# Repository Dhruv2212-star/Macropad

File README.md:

this summer vacation i got to know about hackclub's programs and i decided to take up a challenge to stop bed rotting and learn something new and i found the perfect starting project,
i learnt many skills here such as PCB making, CAD skills and slight firmware making skills. it gave me new set of skills that i'll be using for future projects!

the project i made uses 3x3 key layout in which we can set each key to have a custom function

the project is split into 2 parts:
1. PCB designing
2. CAD designing

PCB designing- is done on kicad where you first make a schematic of the components and you then route the traces to finalise the PCB 
CAD- the case is made using CAD software, it is designed for the pcb to be exposed to keep a hobbyst vibe and also minimal plastic ussage

both of these come together with m3 screws and heat inserts embeded into the PLA case 

Made the sketch in kicad 

finalised the PCB traces and design 

the assembly file 

Made the case in a single piece and with mounts for m3 screws so that it stays in place 

Made the Top case

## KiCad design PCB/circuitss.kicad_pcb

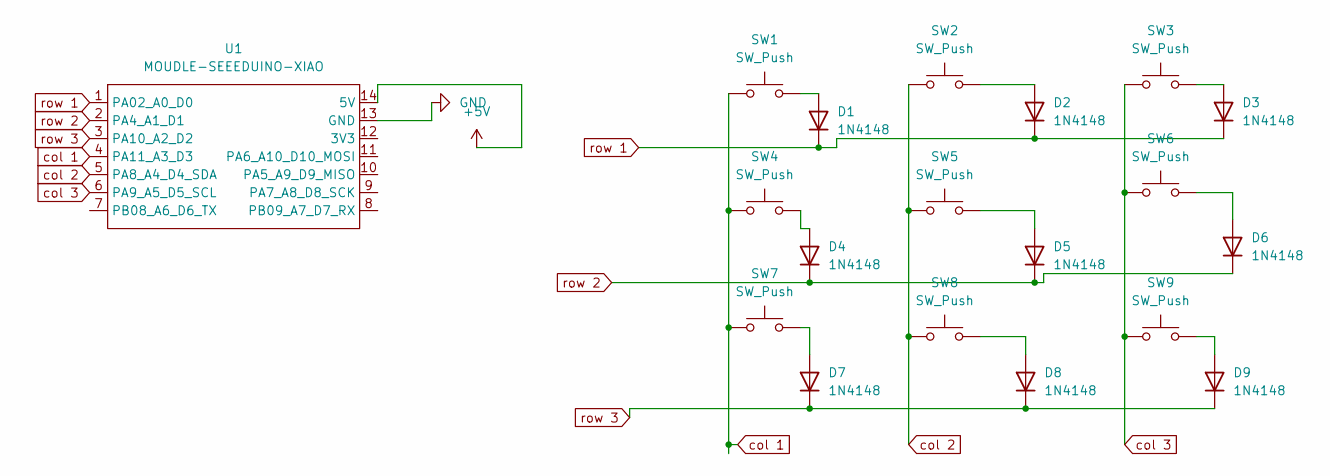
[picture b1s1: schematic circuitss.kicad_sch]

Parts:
D1, D2, D3, D4, D5, D6, D7, D8, D9: 1N4148; D_DO-35_SOD27_P7.62mm_Horizontal
SW1, SW2, SW3, SW4, SW5, SW6, SW7, SW8, SW9: SW_Push; SW_Cherry_MX_1.00u_PCB
U1: MOUDLE-SEEEDUINO-XIAO; XIAO-Generic-Hybrid-14P-2.54-21X17.8MM

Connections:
+5V: U1.14 (5V)
GND: U1.13 (GND)
unnamed: D1.2 (A), SW1.2
unnamed: D2.2 (A), SW2.2
unnamed: D3.2 (A), SW3.2
unnamed: D4.2 (A), SW4.2
unnamed: D5.2 (A), SW5.2
unnamed: D6.2 (A), SW6.2
unnamed: D7.2 (A), SW7.2
unnamed: D8.2 (A), SW8.2
unnamed: D9.2 (A), SW9.2
col 1: SW1.1, SW4.1, SW7.1, U1.4 (PA11_A3_D3)
col 2: SW2.1, SW5.1, SW8.1, U1.5 (PA8_A4_D4_SDA)
col 3: SW3.1, SW6.1, SW9.1, U1.6 (PA9_A5_D5_SCL)
row 1: D1.1 (K), D2.1 (K), D3.1 (K), U1.1 (PA02_A0_D0)
row 2: D4.1 (K), D5.1 (K), D6.1 (K), U1.2 (PA4_A1_D1)
row 3: D7.1 (K), D8.1 (K), D9.1 (K), U1.3 (PA10_A2_D2)

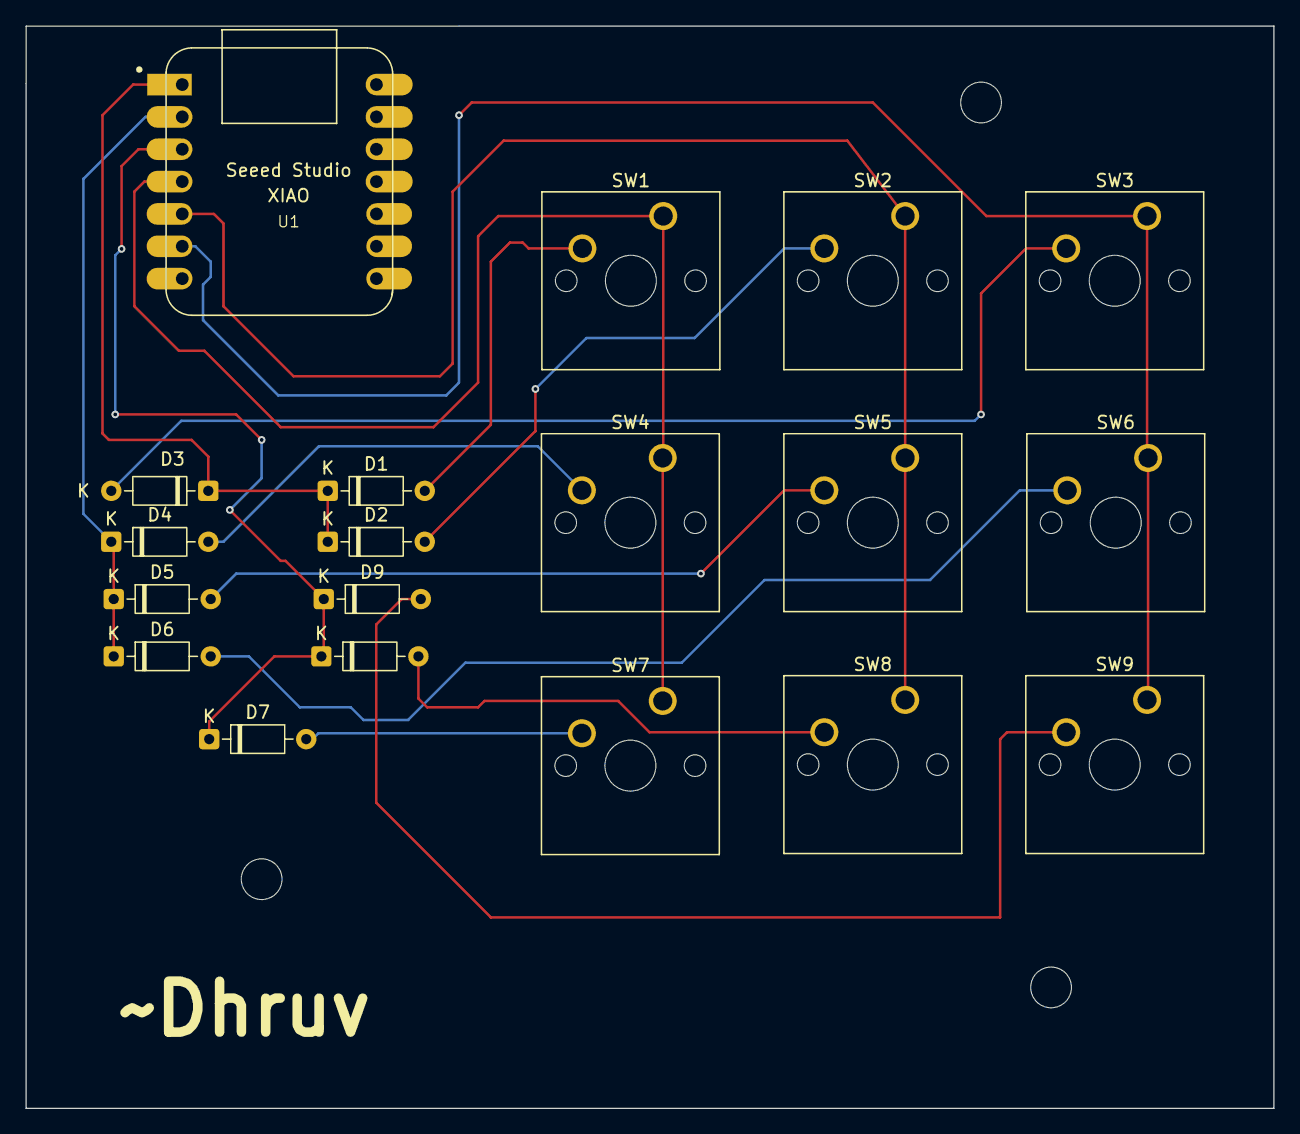
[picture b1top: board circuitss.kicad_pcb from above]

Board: 2 copper layers, 98.0 x 85.0 mm, 19 parts (0 on the bottom side), 15 nets.

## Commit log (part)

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2026-06-20 Initial commit with KiCad files, Gerbers, and 3D case model
2026-06-20 Document 3x3 macropad project in README
    Added details about a 3x3 macropad project including design, assembly, and bill of materials.
2026-06-20 Revise bill of materials with component quantities
    Updated the bill of materials with quantities for components.
2026-06-20 Add main.py with 3x3 layout and custom keymap
2026-06-20 firmware upadate
2026-06-21 Updated macropad case
2026-06-21 Add images and update assembly file details in README
2026-06-21 updated the assembly file
